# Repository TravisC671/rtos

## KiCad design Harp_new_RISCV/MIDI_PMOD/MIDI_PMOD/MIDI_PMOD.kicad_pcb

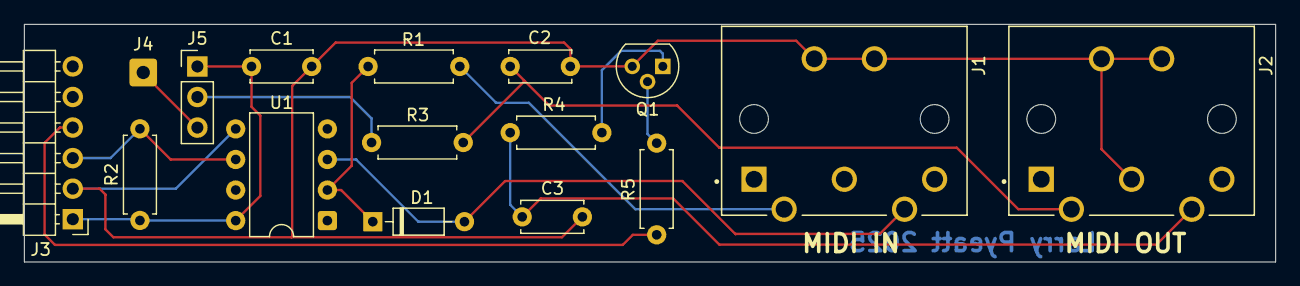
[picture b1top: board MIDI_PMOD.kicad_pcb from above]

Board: 2 copper layers, 104.0 x 19.8 mm, 16 parts (0 on the bottom side), 12 nets.

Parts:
C1: 100n; C_Disc_D5.0mm_W2.5mm_P5.00mm
C2, C3: 100p; C_Disc_D5.0mm_W2.5mm_P5.00mm
D1: 1N4148; D_DO-35_SOD27_P7.62mm_Horizontal
J1, J2: 61PC5FS; SWITCHCRAFT_61PC5FS
J3: 6 pin header; PinHeader_1x06_P2.54mm_Horizontal
J4: +5V; SolderWire-0.5sqmm_1x01_D0.9mm_OD2.3mm
J5: 3 pin header; PinHeader_1x03_P2.54mm_Vertical
Q1: 2N5551; TO-92
R1, R3, R4: 220; R_Axial_DIN0207_L6.3mm_D2.5mm_P7.62mm_Horizontal
R2, R5: 1K; R_Axial_DIN0207_L6.3mm_D2.5mm_P7.62mm_Horizontal
U1: 6N137; DIP-8_W7.62mm

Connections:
GND: C1.2, C2.2, C3.2, J1.G1 (GND), J1.G2 (GND), J2.3, J2.G1 (GND), J2.G2 (GND), J3.2, Q1.3 (E), U1.5 (GND)
unnamed: C2.1, J2.2, R3.2
unnamed: C3.1, J2.4, R4.1
unnamed: D1.2 (A), J1.4, U1.3 (C)
unnamed: D1.1 (K), R1.1, U1.2 (A)
unnamed: C1.1, J3.1, J5.1, R2.1, U1.8 (VCC)
unnamed: J3.3, R2.2, U1.6 (VO)
unnamed: J3.4, R5.2
unnamed: J4.1, J5.3
unnamed: J5.2, R3.1
unnamed: Q1.2 (B), R5.1
unnamed: Q1.1 (C), R4.2

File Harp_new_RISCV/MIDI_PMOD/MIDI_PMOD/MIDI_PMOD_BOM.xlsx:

Reference | Qty | Value | DNP | Exclude from BOM | Exclude from Board | Part | Source
C1 | 1 | 100n |  |  |  | K104K15X7RF5WH5 | Mouser | 0.15
C2,C3 | 2 | 100p |  |  |  | 594-K101J15C0GF5TH5 | Mouser
D1 | 1 | 1N4148 |  |  |  | 512-1N4148 | Mouser
J1,J2 | 2 | 61PC5FS |  |  | Excluded from board | 502-61PC5FS | Mouser
J3 | 1 | 6 pin header |  |  |  | 649-68015-206HLF | Mouser
J4 | 1 | +5V |  | Excluded from BOM
J5 | 1 | 3 pin header |  |  |  | 523-G800WC305018EU | Mouser
Q1 | 1 | 2N5551 |  |  |  | 637-2N5551 | Mouser
R1,R3,R4 | 3 | 220 |  |  |  | 660-MF1/4LCT52R221J | Mouser
R2,R5 | 2 | 1K |  |  |  | 660-MF1/4LCT52R102J | Mouser
U1 | 1 | 6N137 |  |  |  | 859-6N137 | Mouser
S1 | 1 | Shunt |  |  |  | 538-15-29-1027 | Mouser

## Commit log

2026-02-19 initial commit with all my labs
2026-02-20 starting doom port
2026-02-25 working on changing the processor to riscV
    this should give higher performance when accessing ddr2 because of it's
    caching
2026-03-09 Risc V Freertos is going!
2026-03-26 added examples and working on port
2026-03-27 here it goes again
2026-04-20 stuffs
2026-04-23 figuring out timer interupt
2026-04-27 doomloader is running!
2026-04-30 tis running
2026-05-08 the loader and program are running
2026-05-09 I ALMOST LOST EVERYTHING
2026-05-09 done for today
2026-05-09 Large part of it is working (thanks claude)
    Claude only helped with the linker script but I'm so glad I dont need to
    deal with that right now
2026-05-11 closer
